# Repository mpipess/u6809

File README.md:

# u6809

## Project Description

This project allowed me to follow along with Ben Eater's 6502 series while still doing original work.
Architecturally, both systems are similar in scope, but use different components.

I originally intended for this to be a breadboard computer forever, but the temptation to tweak the design was too strong.
Solidifying it as a PCB allowed me to feel "done" with it.

## Primary Components

1. Motorola MC6809E (microprocessor)
2. Motorola MC6821 (peripheral interface adapter)
3. Motorola MC6840 (programmable timer module)
4. Motorola MC6850 (asynchronous communications interface adapter)
5. Alliance AS6C6264 (8 KB SRAM)
6. Winbond W27C512 (64 KB EEPROM)

## Project Status

I froze the design sometime in early Spring 2024 in order to focus on other things. It works well enough to blink some lights, but I haven't tested everything, especially the ACIA.

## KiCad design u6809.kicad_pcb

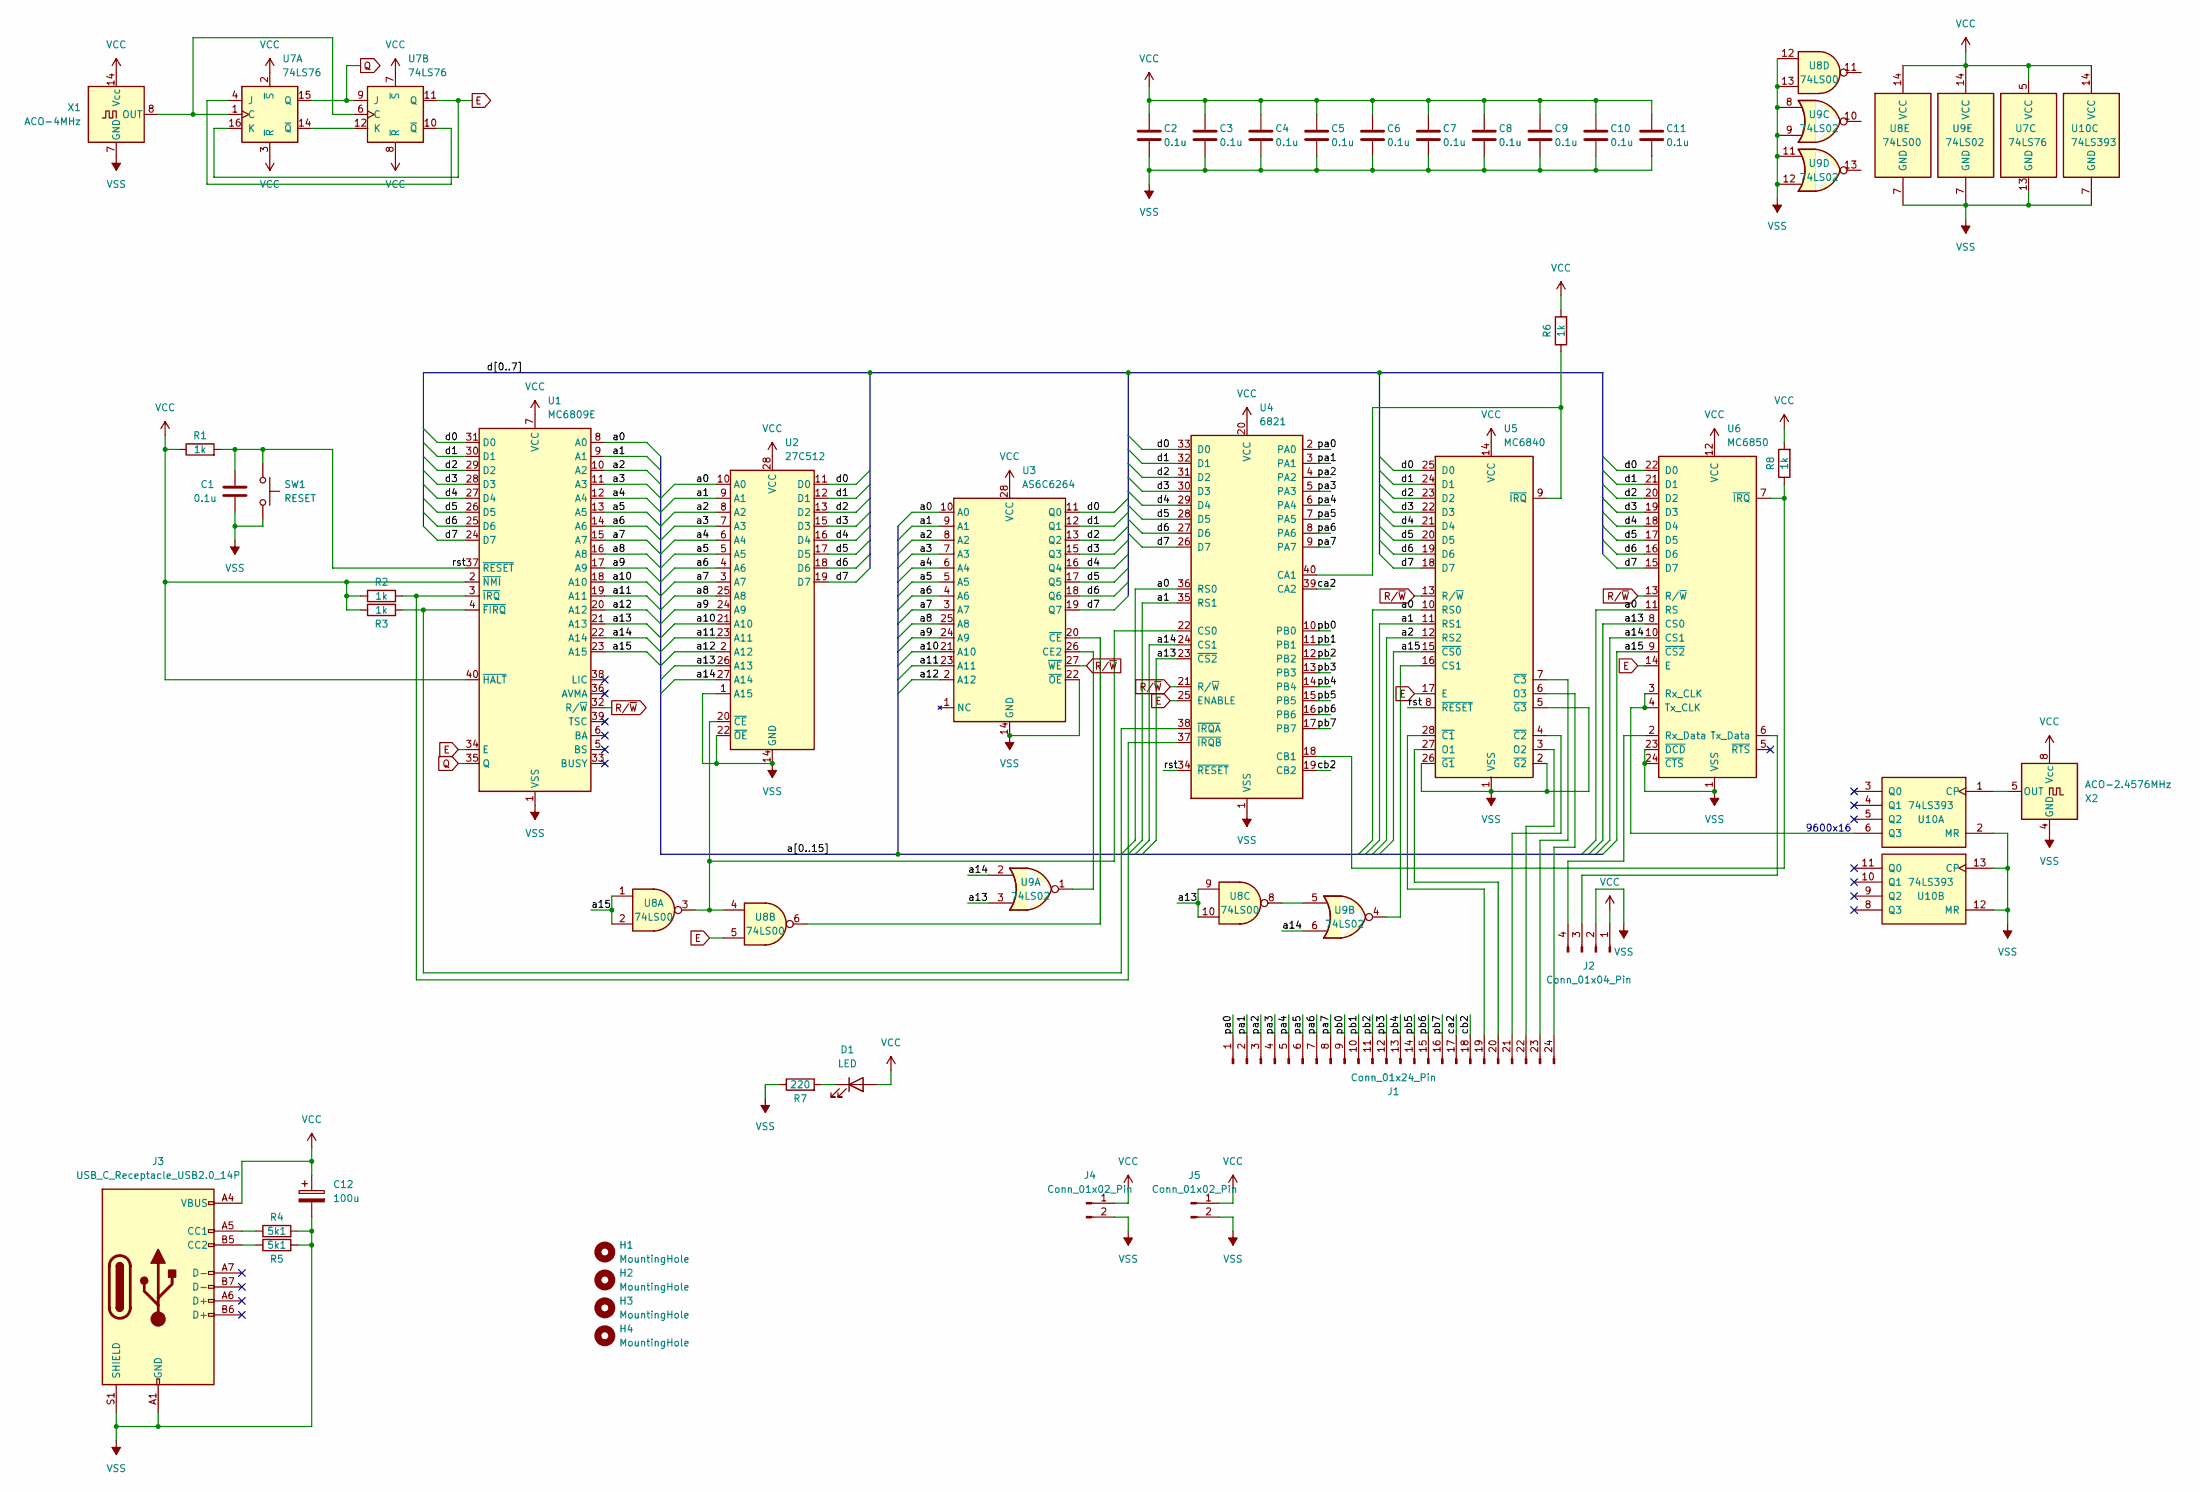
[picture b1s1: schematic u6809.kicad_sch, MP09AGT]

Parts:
C1, C2, C3, C4, C5, C6, C7, C8, C9, C10, C11: 0.1u; C_Disc_D4.3mm_W1.9mm_P5.00mm
C12: 100u; CP_Radial_D10.0mm_P5.00mm
D1: LED; LED_D3.0mm
H1, H2, H3, H4: MountingHole; MountingHole_3.2mm_M3
J1: Conn_01x24_Pin; PinHeader_1x24_P2.54mm_Vertical
J2: Conn_01x04_Pin; PinHeader_1x04_P2.54mm_Vertical
J3: USB_C_Receptacle_USB2.0_14P; USB_C_Receptacle_HRO_TYPE-C-31-M-12
J4, J5: Conn_01x02_Pin; PinHeader_1x02_P2.54mm_Vertical
R1, R2, R3, R6, R8: 1k; R_Axial_DIN0207_L6.3mm_D2.5mm_P7.62mm_Horizontal
R4, R5: 5k1; R_Axial_DIN0207_L6.3mm_D2.5mm_P7.62mm_Horizontal
R7: 220; R_Axial_DIN0207_L6.3mm_D2.5mm_P7.62mm_Horizontal
SW1: RESET; SW_PUSH_6mm
U1: MC6809E; DIP-40_W15.24mm_Socket
U2: 27C512; DIP-28_W15.24mm_Socket
U3: AS6C6264; DIP-28_W15.24mm_Socket
U4: 6821; DIP-40_W15.24mm_Socket
U5: MC6840; DIP-28_W15.24mm_Socket
U6: MC6850; DIP-24_W15.24mm_Socket
U7: 74LS76; DIP-16_W7.62mm_Socket
U8: 74LS00; DIP-14_W7.62mm_Socket
U9: 74LS02; DIP-14_W7.62mm_Socket
U10: 74LS393; DIP-14_W7.62mm_Socket
X1: ACO-4MHz; Oscillator_DIP-14
X2: ACO-2.4576MHz; Oscillator_DIP-8

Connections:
/a0: U1.8 (A0), U2.10 (A0), U3.10 (A0), U4.36 (RS0), U5.10 (RS0), U6.11 (RS)
/a1: U1.9 (A1), U2.9 (A1), U3.9 (A1), U4.35 (RS1), U5.11 (RS1)
/a2: U1.10 (A2), U2.8 (A2), U3.8 (A2), U5.12 (RS2)
/a3: U1.11 (A3), U2.7 (A3), U3.7 (A3)
/a4: U1.12 (A4), U2.6 (A4), U3.6 (A4)
/a5: U1.13 (A5), U2.5 (A5), U3.5 (A5)
/a6: U1.14 (A6), U2.4 (A6), U3.4 (A6)
/a7: U1.15 (A7), U2.3 (A7), U3.3 (A7)
/a8: U1.16 (A8), U2.25 (A8), U3.25 (A8)
/a9: U1.17 (A9), U2.24 (A9), U3.24 (A9)
/a10: U1.18 (A10), U2.21 (A10), U3.21 (A10)
/a11: U1.19 (A11), U2.23 (A11), U3.23 (A11)
/a12: U1.20 (A12), U2.2 (A12), U3.2 (A12)
/a13: U1.21 (A13), U2.26 (A13), U4.23 (~CS2), U6.8 (CS0), U8.9, U8.10, U9.3
/a14: U1.22 (A14), U2.27 (A14), U4.24 (CS1), U6.10 (CS1), U9.2, U9.6
/a15: U1.23 (A15), U5.15 (~CS0), U6.9 (~CS2), U8.1, U8.2
/ca2: J1.17, U4.39 (CA2)
/cb2: J1.18, U4.19 (CB2)
/d0: U1.31 (D0), U2.11 (D0), U3.11 (Q0), U4.33 (D0), U5.25 (D0), U6.22 (D0)
/d1: U1.30 (D1), U2.12 (D1), U3.12 (Q1), U4.32 (D1), U5.24 (D1), U6.21 (D1)
/d2: U1.29 (D2), U2.13 (D2), U3.13 (Q2), U4.31 (D2), U5.23 (D2), U6.20 (D2)
/d3: U1.28 (D3), U2.15 (D3), U3.15 (Q3), U4.30 (D3), U5.22 (D3), U6.19 (D3)
/d4: U1.27 (D4), U2.16 (D4), U3.16 (Q4), U4.29 (D4), U5.21 (D4), U6.18 (D4)
/d5: U1.26 (D5), U2.17 (D5), U3.17 (Q5), U4.28 (D5), U5.20 (D5), U6.17 (D5)
/d6: U1.25 (D6), U2.18 (D6), U3.18 (Q6), U4.27 (D6), U5.19 (D6), U6.16 (D6)
/d7: U1.24 (D7), U2.19 (D7), U3.19 (Q7), U4.26 (D7), U5.18 (D7), U6.15 (D7)
/pa0: J1.1, U4.2 (PA0)
/pa1: J1.2, U4.3 (PA1)
/pa2: J1.3, U4.4 (PA2)
/pa3: J1.4, U4.5 (PA3)
/pa4: J1.5, U4.6 (PA4)
/pa5: J1.6, U4.7 (PA5)
/pa6: J1.7, U4.8 (PA6)
/pa7: J1.8, U4.9 (PA7)
/pb0: J1.9, U4.10 (PB0)
/pb1: J1.10, U4.11 (PB1)
/pb2: J1.11, U4.12 (PB2)
/pb3: J1.12, U4.13 (PB3)
/pb4: J1.13, U4.14 (PB4)
/pb5: J1.14, U4.15 (PB5)
/pb6: J1.15, U4.16 (PB6)
/pb7: J1.16, U4.17 (PB7)
/rst: C1.2, R1.2, SW1.1, U1.37 (~RESET), U4.34 (~RESET), U5.8 (~RESET)
E: U1.34 (E), U4.25 (ENABLE), U5.17 (E), U6.14 (E), U7.11 (Q), U7.16 (K), U8.5
unnamed: D1.1 (K), R7.2
unnamed: J1.19, U5.28 (~C1)
unnamed: J1.20, U5.27 (O1)
unnamed: J1.21, U5.4 (~C2)
unnamed: J1.22, U5.3 (O2)
unnamed: J1.23, U5.7 (~C3)
unnamed: J1.24, U5.6 (O3)
unnamed: J2.3, U6.6 (Tx_Data)
unnamed: J2.4, U6.2 (Rx_Data)
unnamed: J3.A5 (CC1), R4.1
unnamed: J3.B5 (CC2), R5.1
unnamed: R3.2, U1.4 (~FIRQ), U4.38 (~IRQA)
unnamed: R2.2, U1.3 (~IRQ), U4.37 (~IRQB)
unnamed: U2.20 (~CE), U4.22 (CS0), U8.3, U8.4
unnamed: U3.26 (CE2), U9.1
unnamed: U3.20 (~CE), U8.6
unnamed: R6.1, U4.40 (CA1), U5.9 (~IRQ)
unnamed: R8.1, U4.18 (CB1), U6.7 (~IRQ)
unnamed: U5.16 (CS1), U9.4
unnamed: U7.1 (C), U7.6 (C), X1.8 (OUT)
unnamed: U7.4 (J), U7.10 (~Q)
unnamed: U7.12 (K), U7.14 (~Q)
unnamed: U8.8, U9.5
unnamed: U10.1 (CP), X2.5 (OUT)
unnamed: U6.3 (Rx_CLK), U6.4 (Tx_CLK), U10.6 (Q3)
Q: U1.35 (Q), U7.9 (J), U7.15 (Q)
R/~W: U1.32 (R/~W), U3.27 (~WE), U4.21 (R/~W), U5.13 (R/~W), U6.13 (R/~W)
VCC: C2.1, C3.1, C4.1, C5.1, C6.1, C7.1, C8.1, C9.1, C10.1, C11.1, C12.1, D1.2 (A), J2.1, J3.A4 (VBUS), J3.A9 (VBUS), J3.B4 (VBUS), J3.B9 (VBUS), J4.1, J5.1, R1.1, R2.1, R3.1, R6.2, R8.2, U1.2 (~NMI), U1.7 (VCC), U1.40 (~HALT), U2.28 (VCC), U3.28 (VCC), U4.20 (VCC), U5.14 (VCC), U6.12 (VCC), U7.2 (~S), U7.3 (~R), U7.5 (VCC), U7.7 (~S), U7.8 (~R), U8.14 (VCC), U9.14 (VCC), U10.14 (VCC), X1.14 (Vcc), X2.8 (Vcc)
VSS: C1.1, C2.2, C3.2, C4.2, C5.2, C6.2, C7.2, C8.2, C9.2, C10.2, C11.2, C12.2, J2.2, J3.A1 (GND), J3.A12 (GND), J3.B1 (GND), J3.B12 (GND), J3.S1 (SHIELD), J4.2, J5.2, R4.2, R5.2, R7.1, SW1.2, U1.1 (VSS), U2.1 (A15), U2.14 (GND), U2.22 (~OE), U3.14 (GND), U3.22 (~OE), U4.1 (VSS), U5.1 (VSS), U5.2 (~G2), U5.5 (~G3), U5.26 (~G1), U6.1 (VSS), U6.23 (~DCD), U6.24 (~CTS), U7.13 (GND), U8.7 (GND), U8.12, U8.13, U9.7 (GND), U9.8, U9.9, U9.11, U9.12, U10.2 (MR), U10.7 (GND), U10.12 (MR), U10.13 (CP), X1.7 (GND), X2.4 (GND)

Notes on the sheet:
9600x16

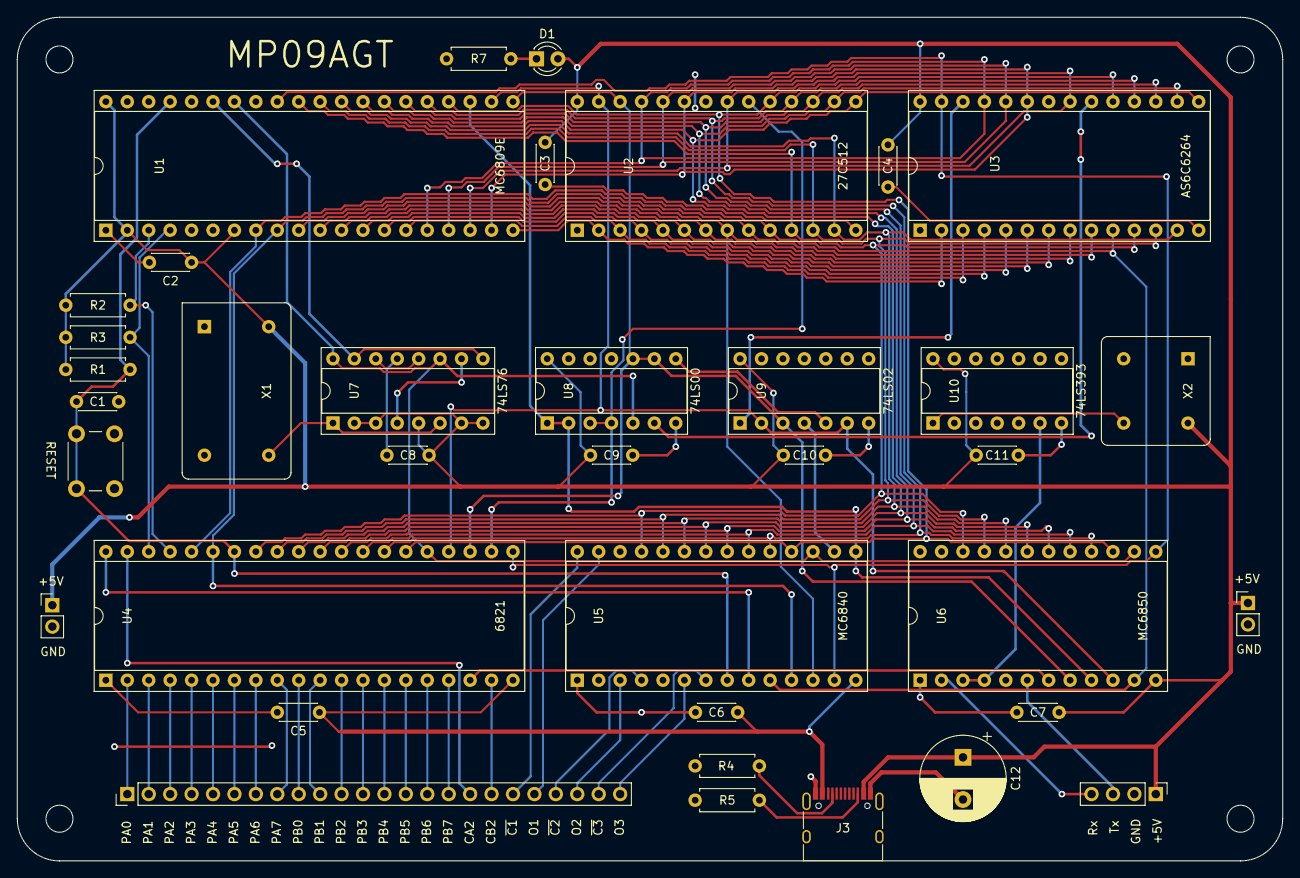
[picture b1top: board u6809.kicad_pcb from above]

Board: 2 copper layers, 150.0 x 100.0 mm, 41 parts (0 on the bottom side), 73 nets.
